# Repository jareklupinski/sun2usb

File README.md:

# sun2usb
An Adapter to connect your Classic keyboard to a modern interface

Met a cool guy in Pittsburgh who asked about retrofitting a couple of keyboards his school was throwing away to work with modern hardware. I got to keep one of the keyboards :)

It's a fun piece of desk history and definitely feels more solid than most keyboards. Using a Teensy as the base makes the USB part super easy.

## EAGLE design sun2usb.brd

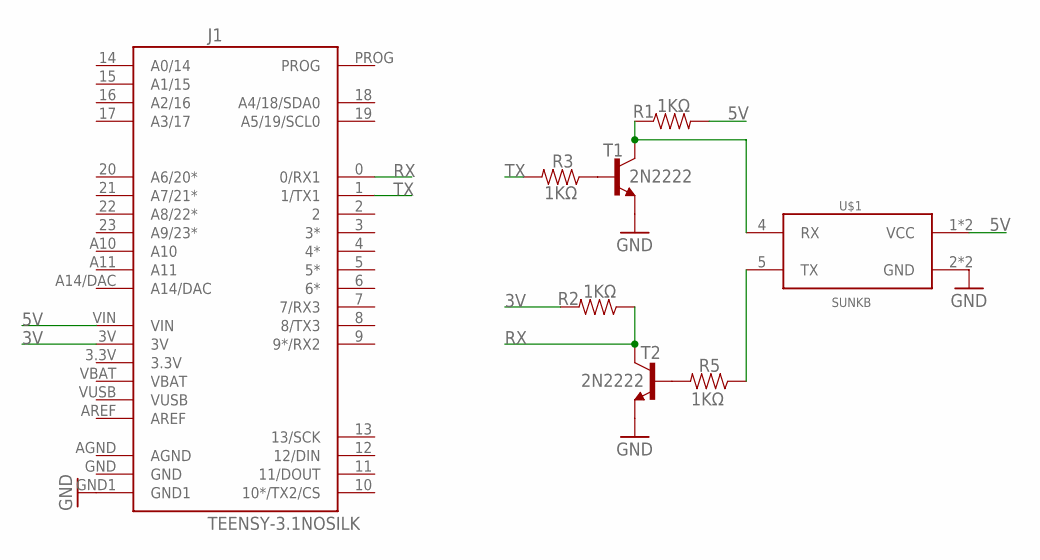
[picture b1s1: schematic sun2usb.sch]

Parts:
J1: TEENSY-3.1NOSILK; TEENSY-3.1_NOSILK
R1, R2, R3, R5: 1KΩ; AXIAL-0.4
T1, T2: 2N2222; TO92-EBC-OVAL
U$1: SUNKB; MINI8DIN

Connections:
3V: J1.3V, R2.P$2 (2)
5V: J1.VIN, R1.P$2 (2), U$1.1 (VCC), U$1.8 (VCC)
GND: J1.GND1, T1.E, T2.E, U$1.2 (GND), U$1.3 (GND)
unnamed: R5.P$1 (1), U$1.5 (TX)
unnamed: R1.P$1 (1), T1.C, U$1.4 (RX)
unnamed: R3.P$1 (1), T1.B
unnamed: R5.P$2 (2), T2.B
RX: J1.0 (0/RX1), R2.P$1 (1), T2.C
TX: J1.1 (1/TX1), R3.P$2 (2)

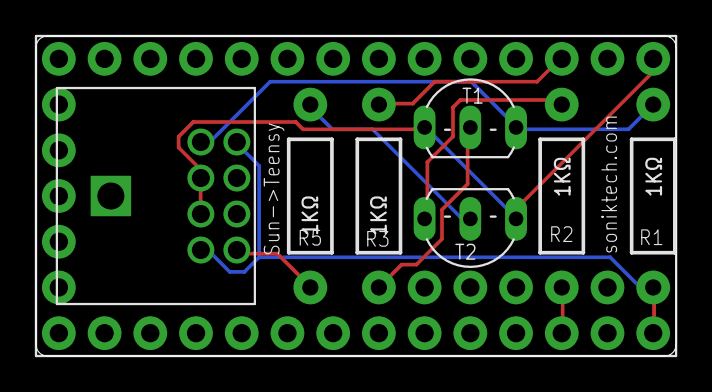
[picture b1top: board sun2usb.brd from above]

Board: 2 copper layers, 35.6 x 17.8 mm, 8 parts (0 on the bottom side), 9 nets.

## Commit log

2018-07-05 design tested: working

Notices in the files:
parts and their libraries:
SparkFun-Boards: Licensing: Creative Commons ShareAlike 4.0 International - https://creativecommons.org/licenses/by-sa/4.0
